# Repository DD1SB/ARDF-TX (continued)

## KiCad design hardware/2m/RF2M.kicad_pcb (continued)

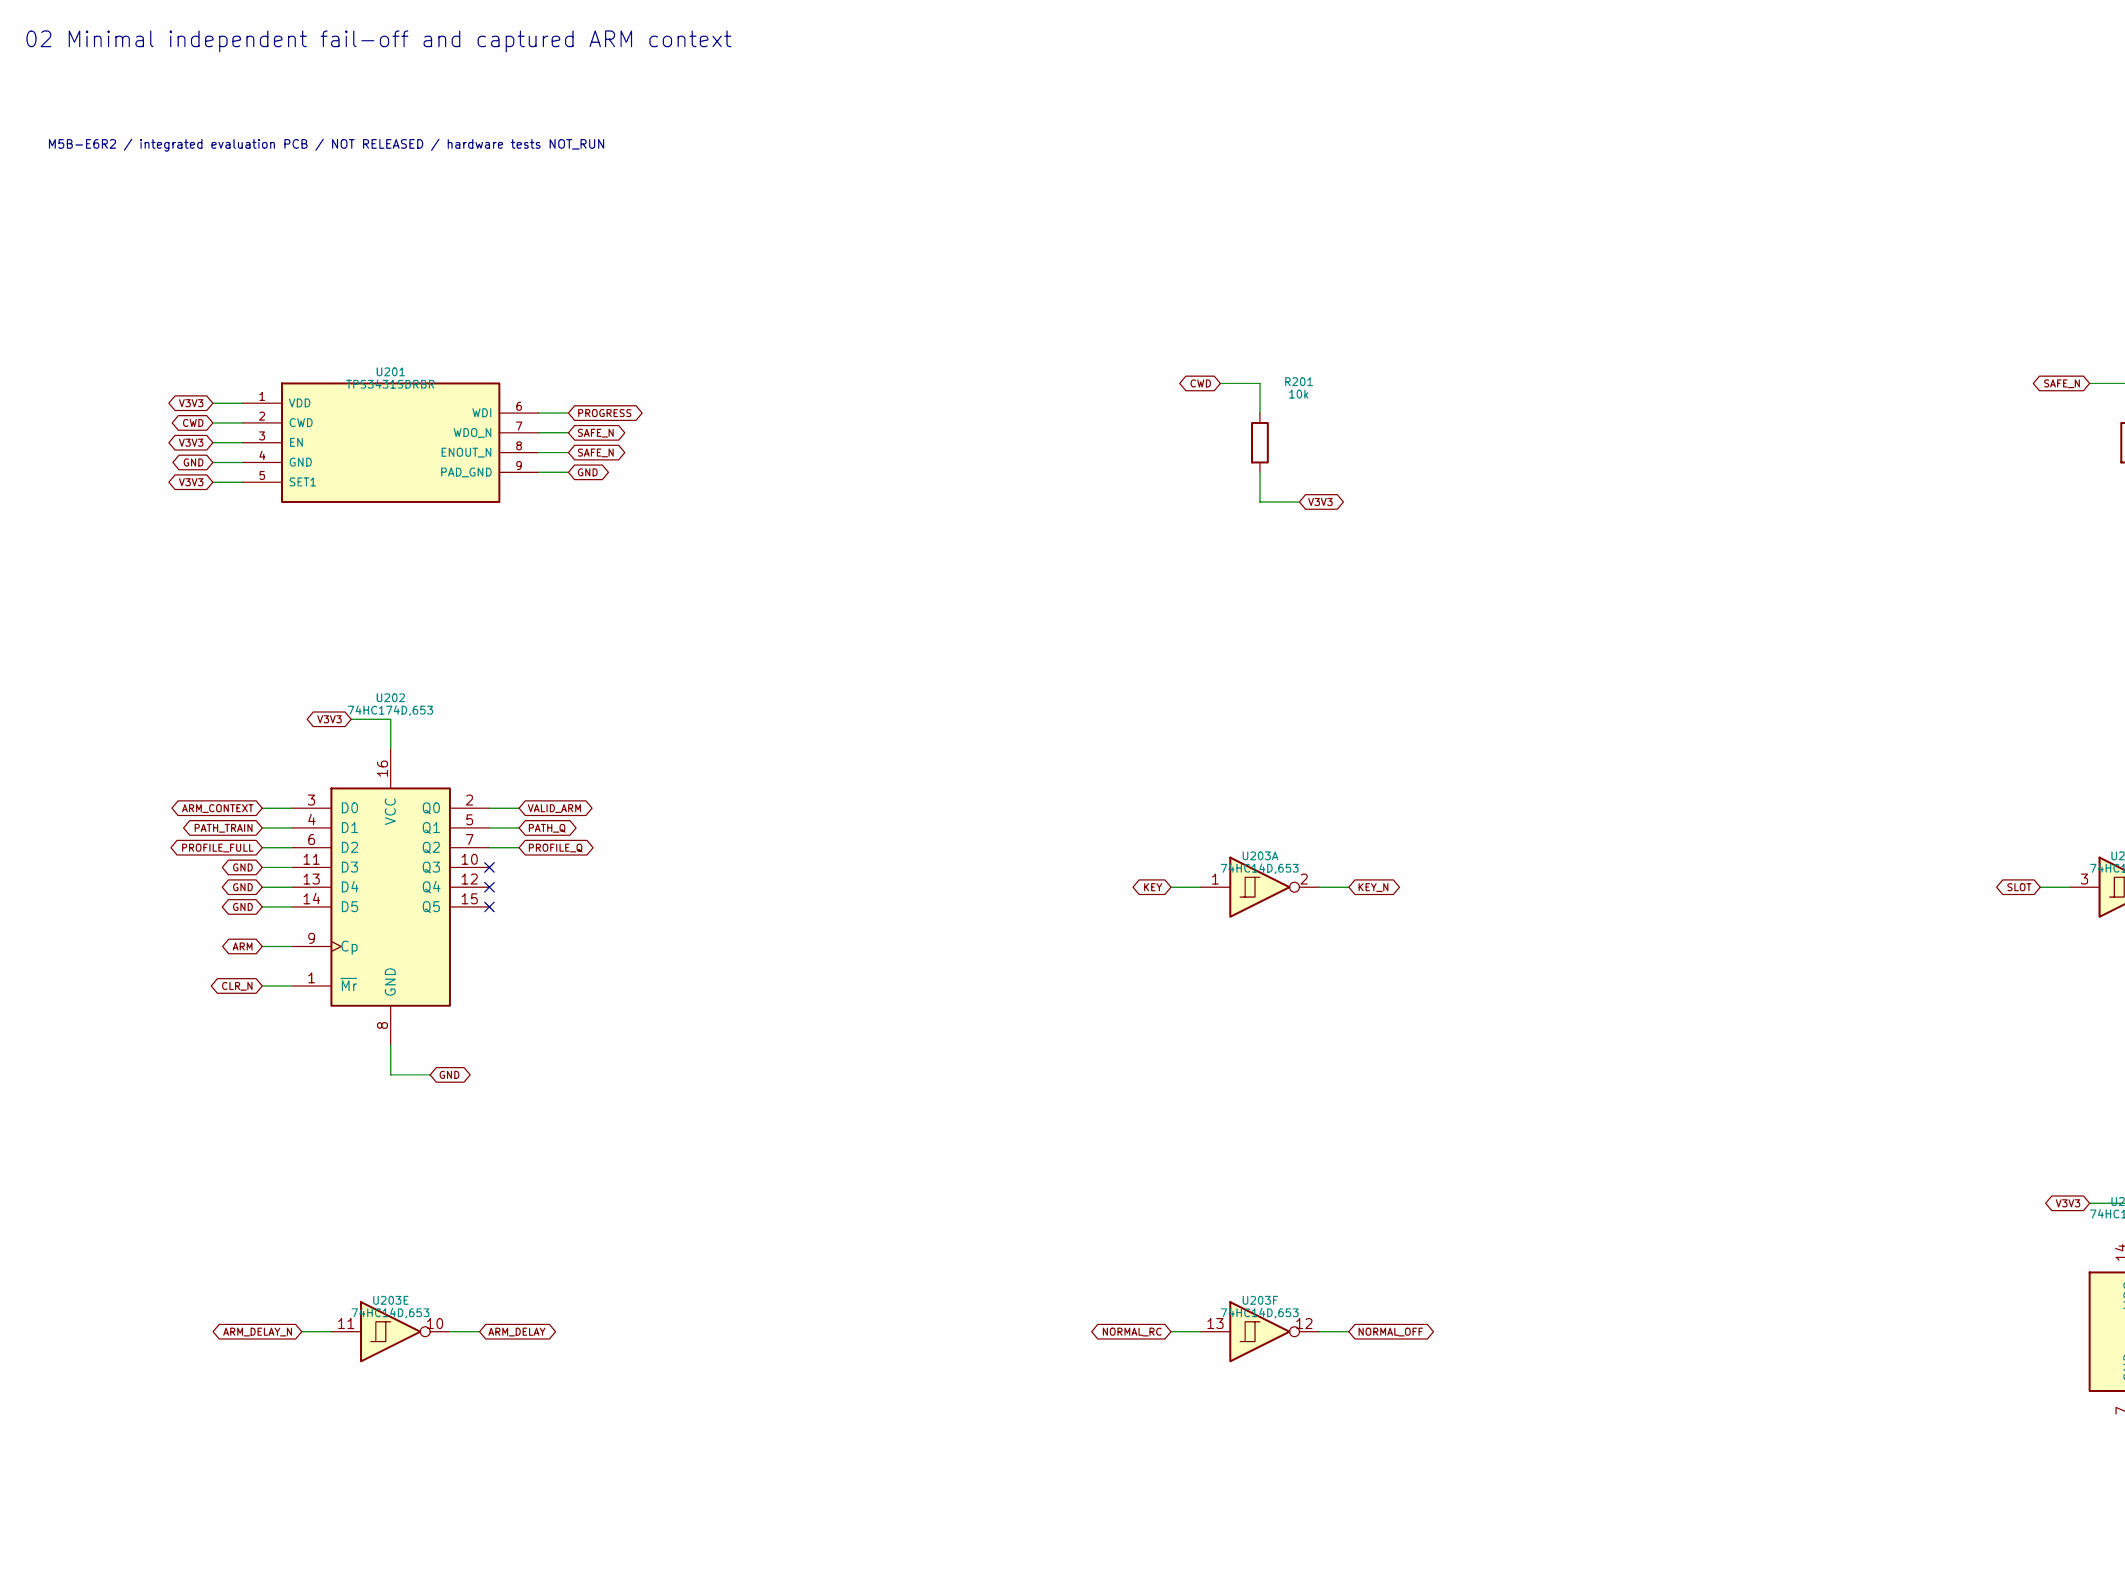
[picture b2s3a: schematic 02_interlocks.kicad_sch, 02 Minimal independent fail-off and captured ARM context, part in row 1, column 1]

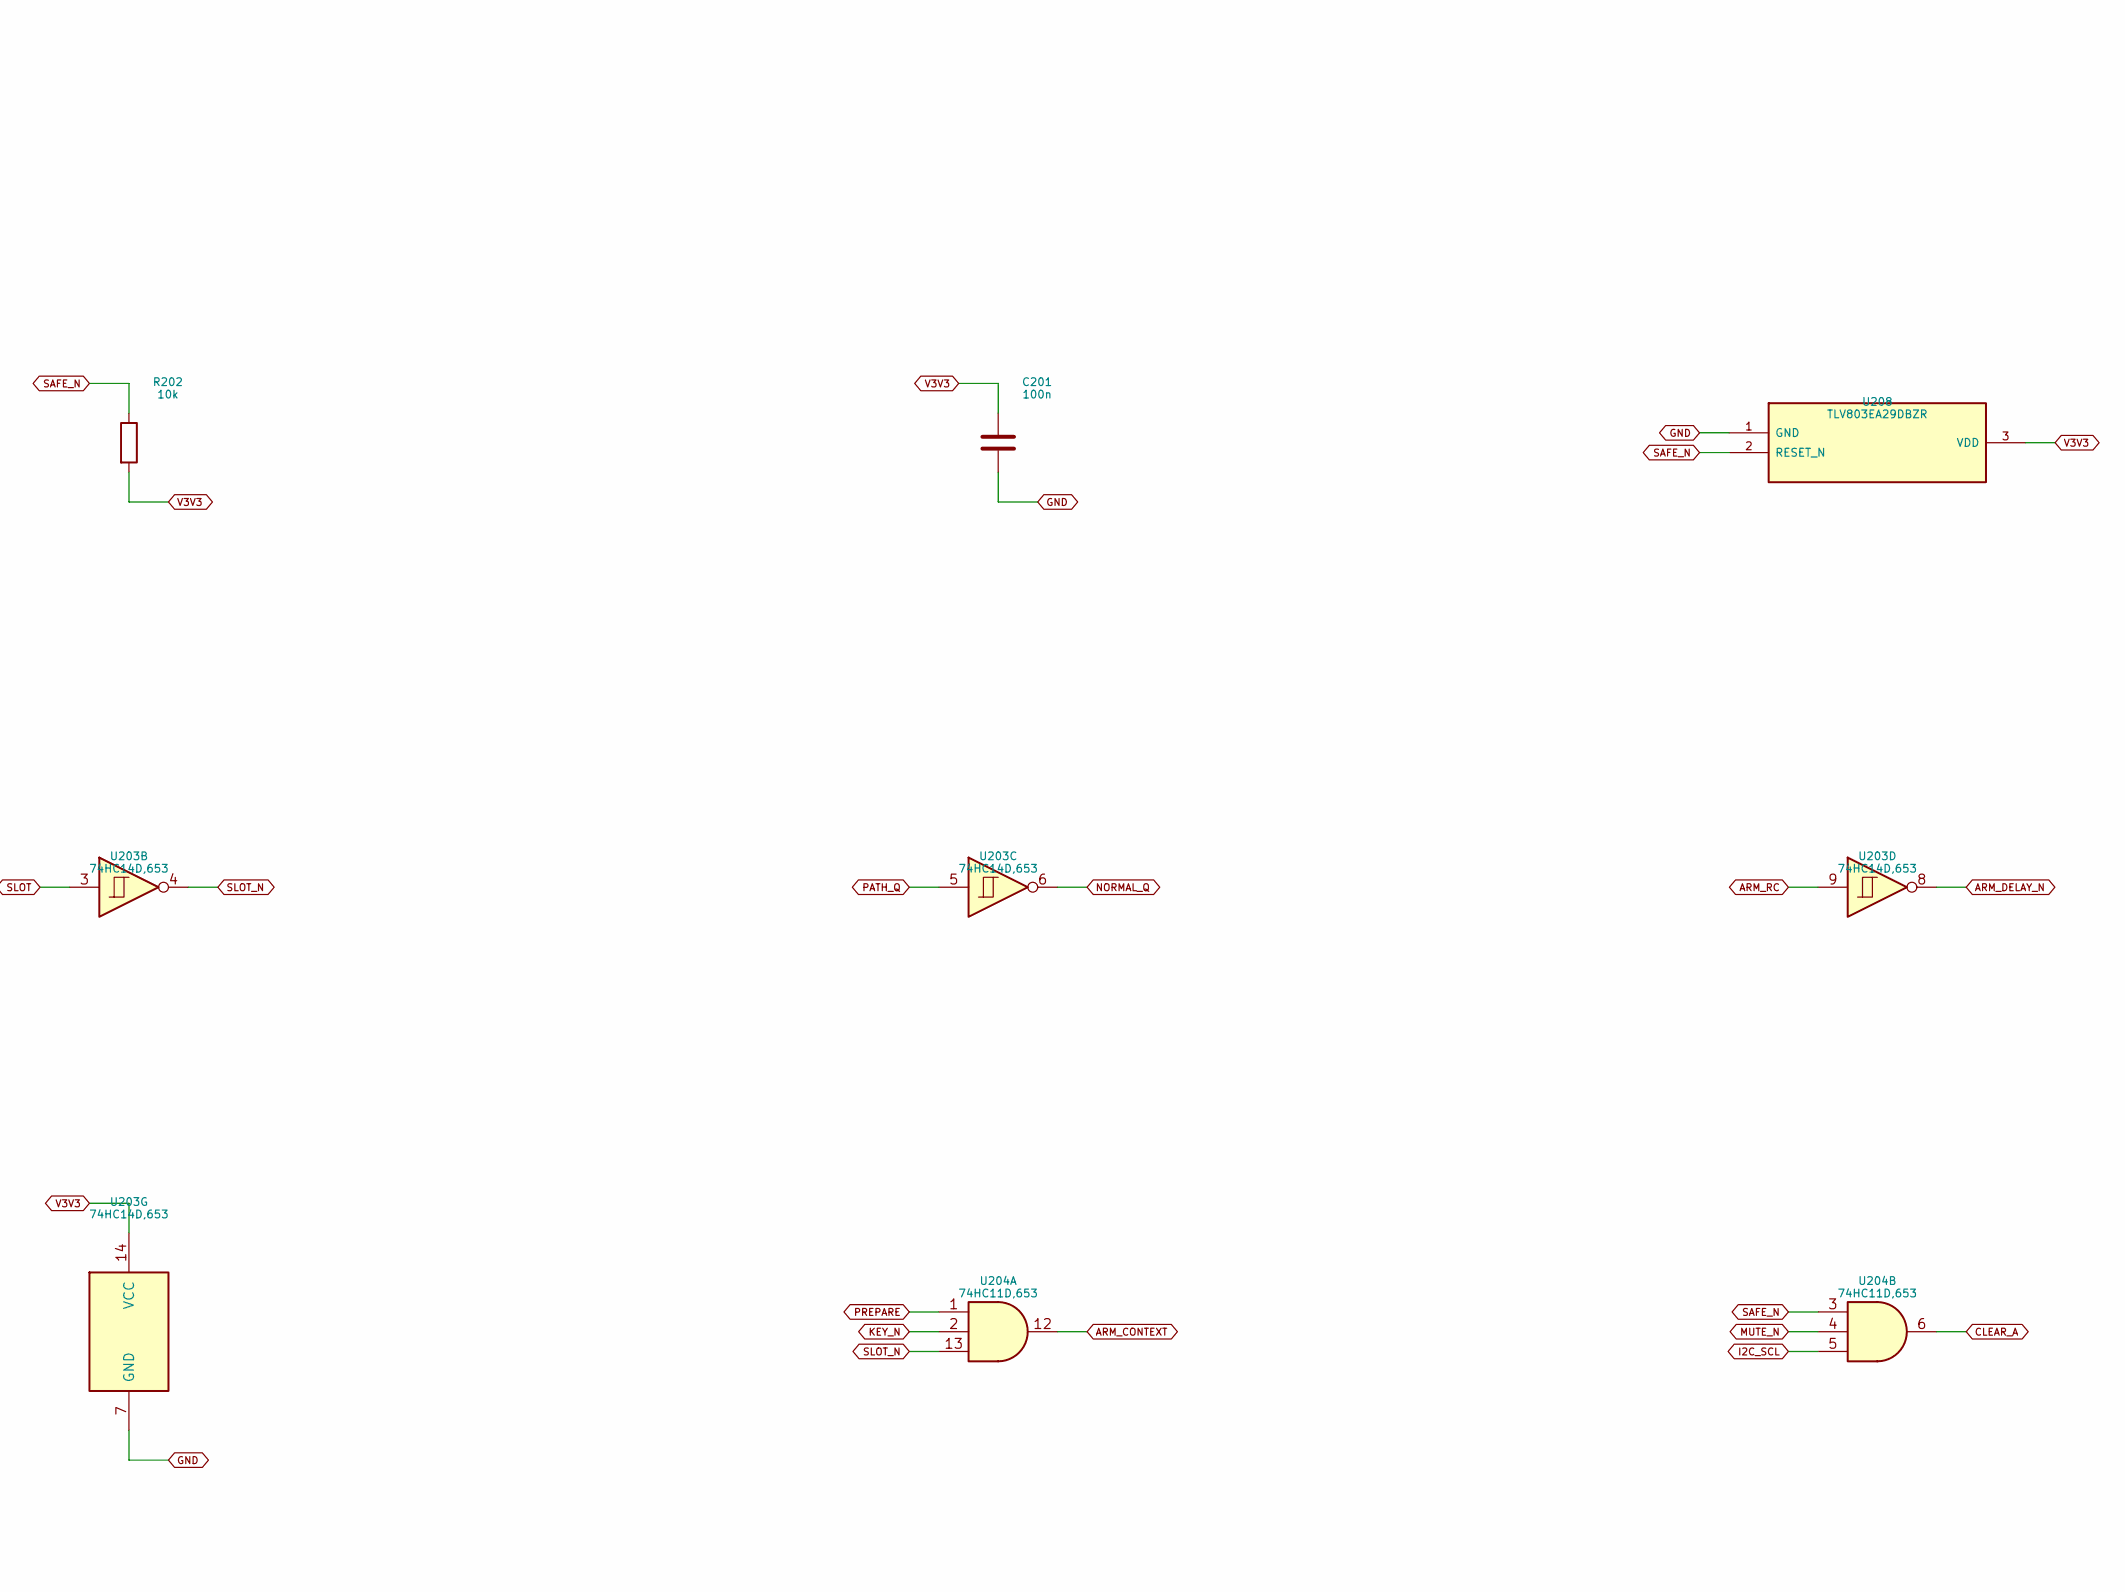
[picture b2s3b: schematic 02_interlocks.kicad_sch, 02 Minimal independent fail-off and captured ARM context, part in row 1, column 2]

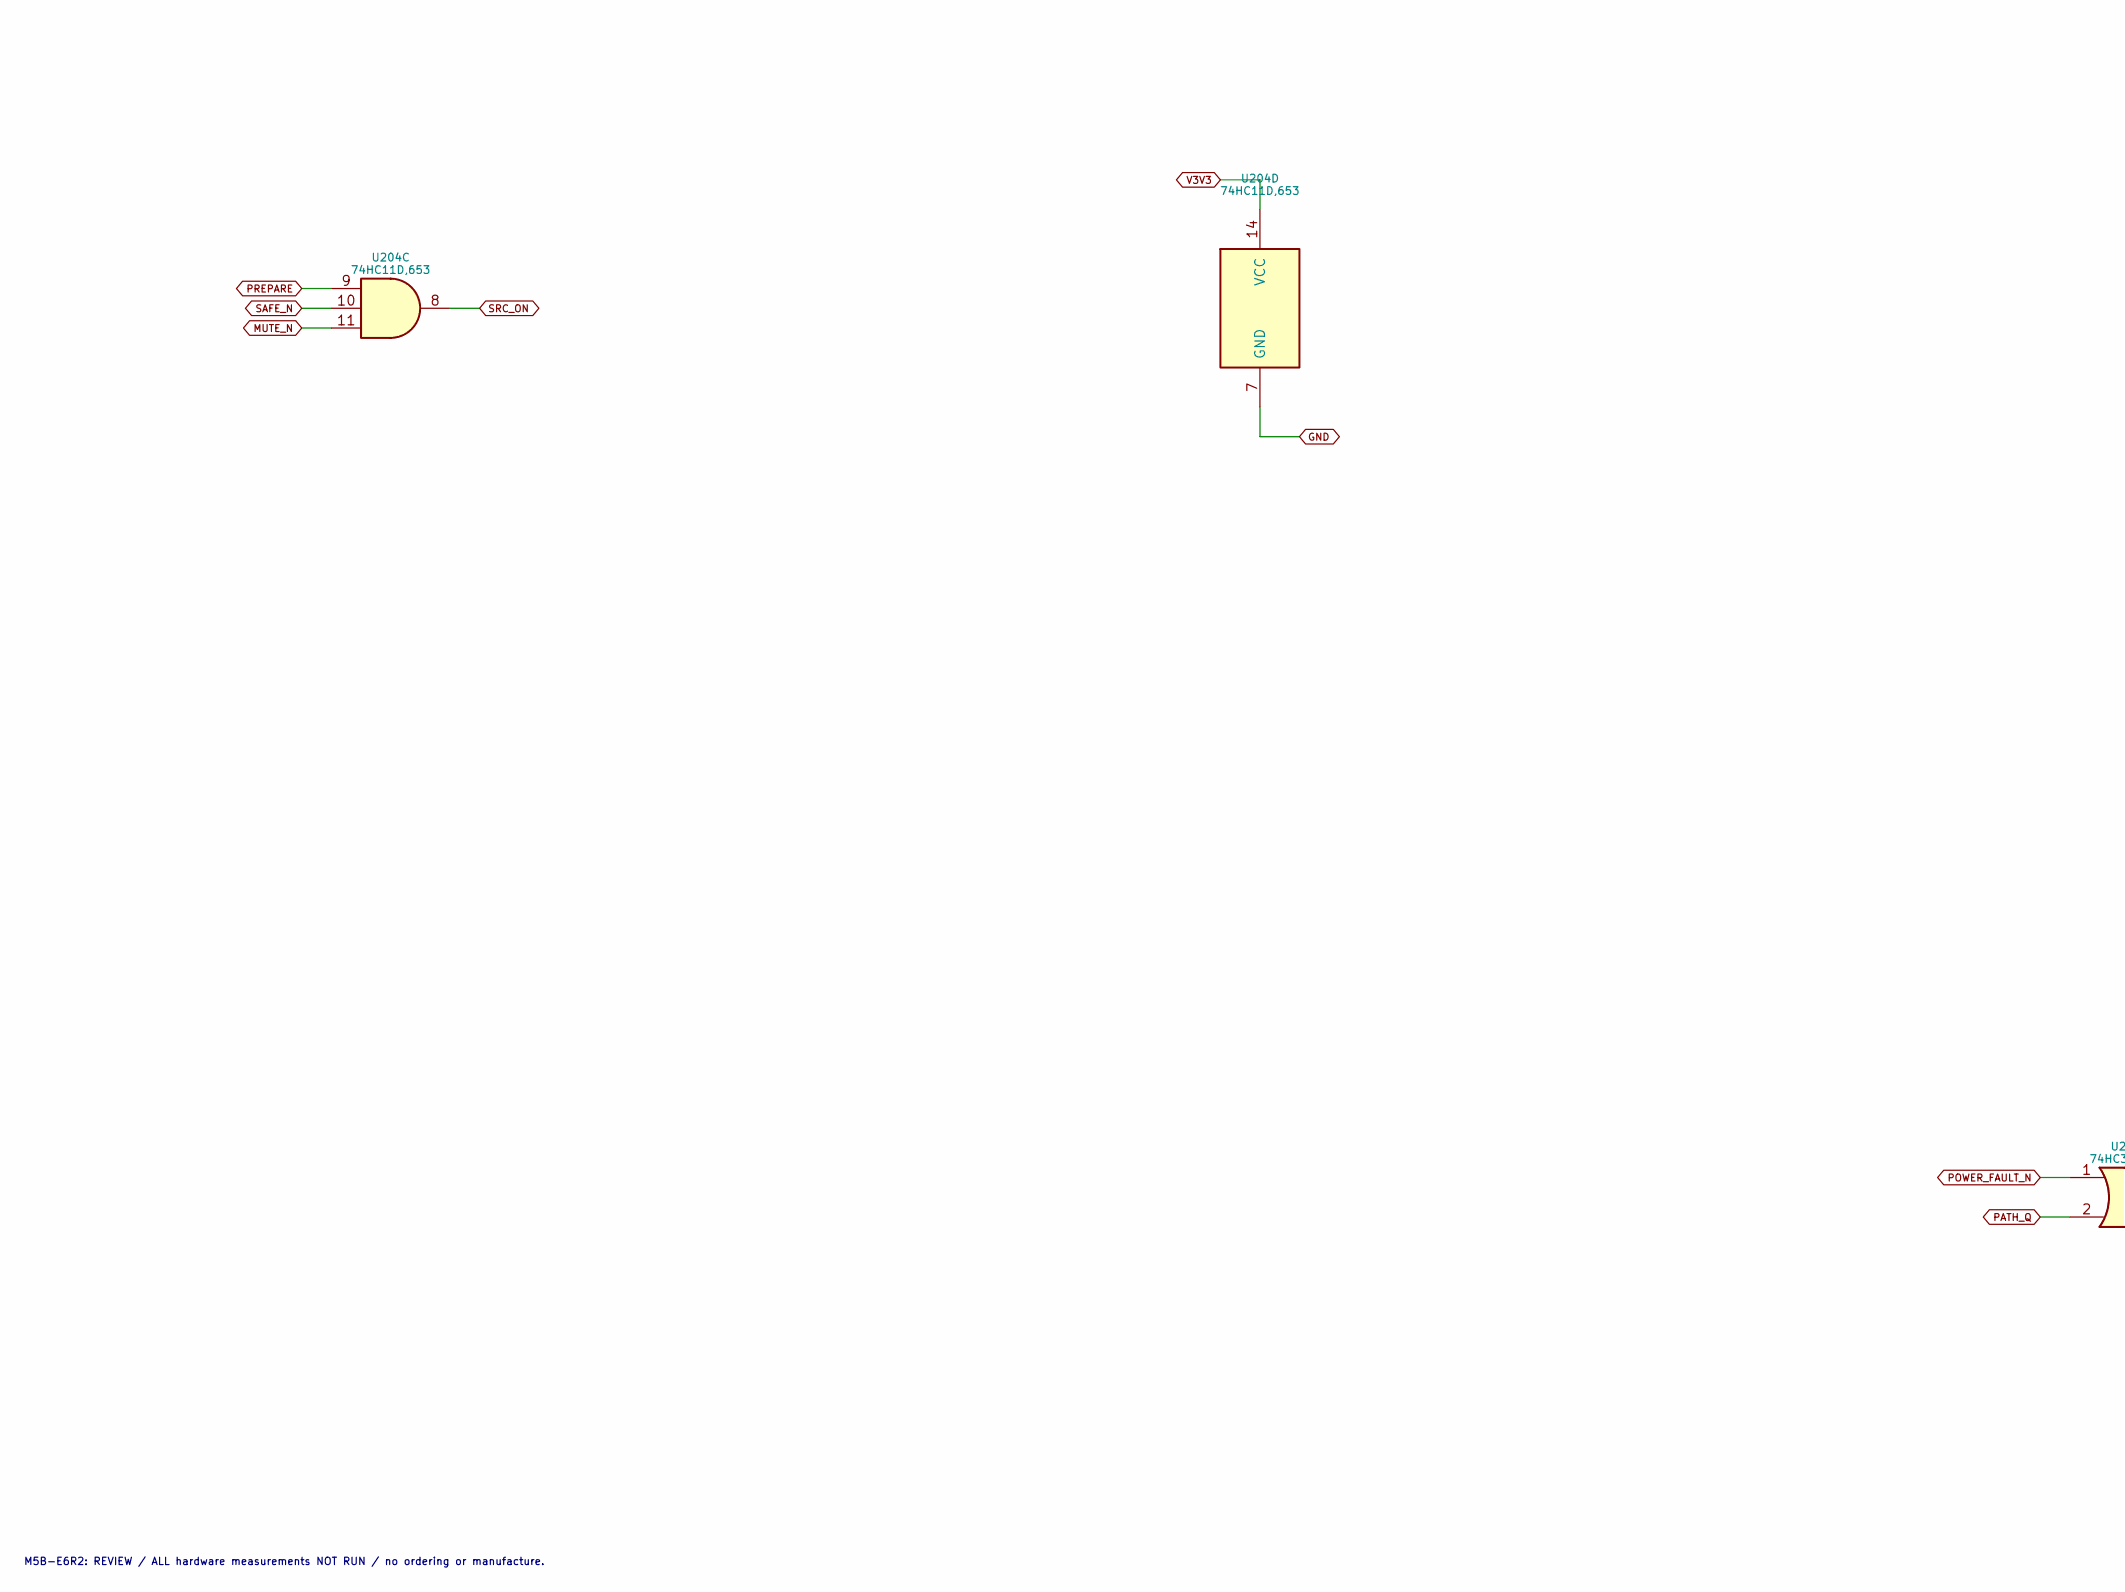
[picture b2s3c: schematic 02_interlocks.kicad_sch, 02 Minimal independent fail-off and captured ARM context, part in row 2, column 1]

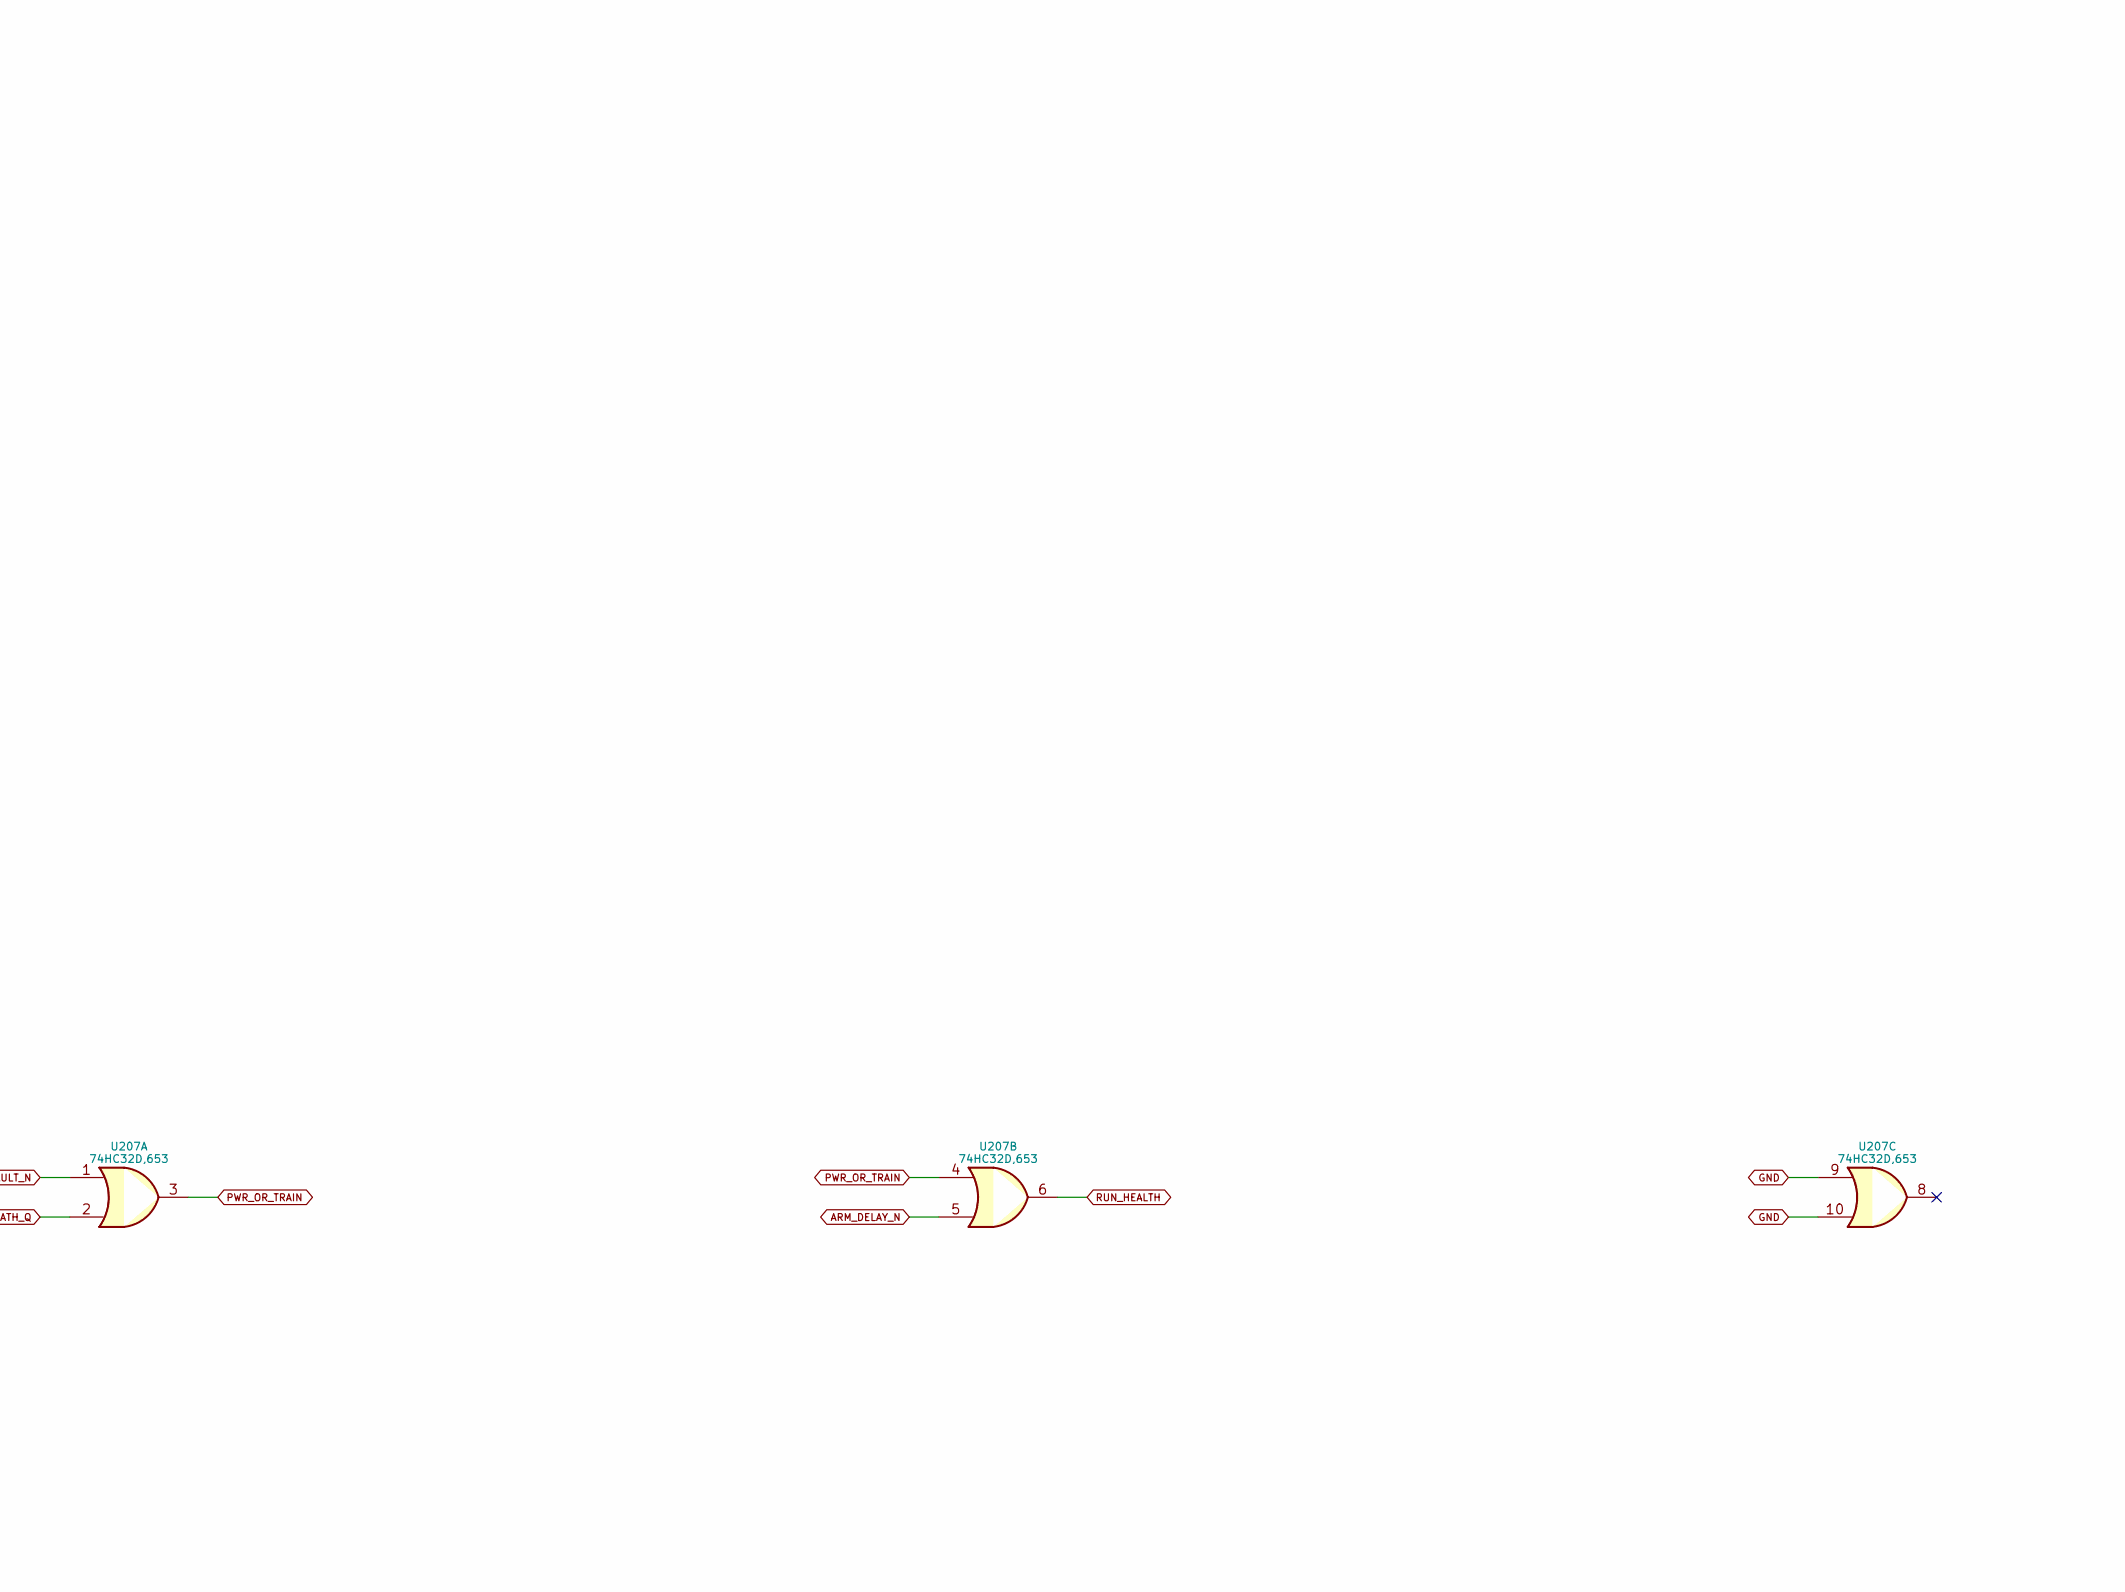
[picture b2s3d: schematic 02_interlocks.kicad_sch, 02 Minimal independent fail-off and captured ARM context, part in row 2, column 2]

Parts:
C201: 100n; C_0603_1608Metric_E3; MPN CC0603KRX7R8BB104
R201, R202: 10k; R_0603_1608Metric_E3; MPN RC0603FR-0710KL
U201: TPS3431SDRBR; VSON-8-1EP_3x3mm_P0.65mm_EP1.65x2.4mm_E3; MPN TPS3431SDRBR
U202: 74HC174D,653; SOIC-16_3.9x9.9mm_P1.27mm_E3; MPN 74HC174D,653
U203: 74HC14D,653; SOIC-14_3.9x8.7mm_P1.27mm_E3; MPN 74HC14D,653
U204: 74HC11D,653; SOIC-14_3.9x8.7mm_P1.27mm_E3; MPN 74HC11D,653
U207: 74HC32D,653; SOIC-14_3.9x8.7mm_P1.27mm_E3; MPN 74HC32D,653
U208: TLV803EA29DBZR; SOT-23_E3; MPN TLV803EA29DBZR

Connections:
ARM: U202.9 (Cp); also elsewhere on the board
ARM_CONTEXT: U202.3 (D0), U204.12
ARM_DELAY: U203.10; also elsewhere on the board
ARM_DELAY_N: U203.8, U203.11, U207.5
ARM_RC: U203.9; also elsewhere on the board
CLEAR_A: U204.6; also elsewhere on the board
CLR_N: U202.1 (~Mr); also elsewhere on the board
CWD: R201.1, U201.2 (CWD)
GND: C201.2, U201.4 (GND), U201.9 (PAD_GND), U202.8 (GND), U202.11 (D3), U202.13 (D4), U202.14 (D5), U203.7 (GND), U204.7 (GND), U207.9, U207.10, U208.1 (GND); also elsewhere on the board
I2C_SCL: U204.5; also elsewhere on the board
KEY: U203.1; also elsewhere on the board
KEY_N: U203.2, U204.2; also elsewhere on the board
MUTE_N: U204.4, U204.11; also elsewhere on the board
NORMAL_OFF: U203.12; also elsewhere on the board
NORMAL_Q: U203.6; also elsewhere on the board
NORMAL_RC: U203.13; also elsewhere on the board
PATH_Q: U202.5 (Q1), U203.5, U207.2; also elsewhere on the board
PATH_TRAIN: U202.4 (D1); also elsewhere on the board
POWER_FAULT_N: U207.1; also elsewhere on the board
PREPARE: U204.1, U204.9; also elsewhere on the board
PROFILE_FULL: U202.6 (D2); also elsewhere on the board
PROFILE_Q: U202.7 (Q2); also elsewhere on the board
PROGRESS: U201.6 (WDI); also elsewhere on the board
PWR_OR_TRAIN: U207.3, U207.4
RUN_HEALTH: U207.6; also elsewhere on the board
SAFE_N: R202.1, U201.7 (WDO_N), U201.8 (ENOUT_N), U204.3, U204.10, U208.2 (RESET_N); also elsewhere on the board
SLOT: U203.3; also elsewhere on the board
SLOT_N: U203.4, U204.13
SRC_ON: U204.8; also elsewhere on the board
V3V3: C201.1, R201.2, R202.2, U201.1 (VDD), U201.3 (EN), U201.5 (SET1), U202.16 (VCC), U203.14 (VCC), U204.14 (VCC), U208.3 (VDD); also elsewhere on the board
VALID_ARM: U202.2 (Q0); also elsewhere on the board

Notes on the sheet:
02 Minimal independent fail-off and captured ARM context
M5B-E6R2 / integrated evaluation PCB / NOT RELEASED / hardware tests NOT_RUN
M5B-E6R2: REVIEW / ALL hardware measurements NOT RUN / no ordering or manufacture.
